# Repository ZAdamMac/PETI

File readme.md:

# PETI Virtual Pet Development Project

## Introduction

PETI is a project to create a bespoke, retro-styled Virtual Pet running on the MSP430FR5994 microcontroller, along with a number of late-project goals to add functionality that is useful for demonstrating the sort of Hardware Hacking concepts useful in (i.e.) DEFCON Badge Challenges.

Full documentation is available as part of the "documentation" directory of this repo. A suite of helper tools is present [here](https://github.com/zadammac/peti-helpers)

This project involves both firmware and hardware development.

## NOTICE: Project on Hiaitus
This project is currently **on hiaitus**. You're stll welcome to submit bug reports (which will be addressed rapidly) or make use of the codebase, but we have a couple of caveats:
- Missing firmware functionality and gameplay features are not currently scheduled to be released. There's some frozen work on the `v/0.6.0` branch and f/ branches originating from it, which starts implementing the next gameplay release.
- It is not currently advisable to mill the development kit boards provided under `hardware`. When the project comes off hiaitus there's going to be a major hardware redesign released, which will be simpler and more elegant.

Currently, we think the project is likely to come off hiaitus sometime around the start of 2027.

## NOTICE: Github End of Life
The version of the project hosted on github is no longer being actively maintained and has been scheduled for truncation (removal of branches and notices apart from this readme file). The authoritative main repository of this project is [Arcana Labs' Forgejo](https://forgejo.arcanalabs.ca/zadammac/peti). Please redirect your upstream branch definitions to that repository. In the days to come, the remaining files from this repository will be removed and purged from the commit history on Github. This has been done because of GitHub's decision to allow for - and encourage - the training of proprietary large language model code generation systems on codebases where the licensing implicitly (or often explicitly) does not permit such conversion.

## Requirements
This project has a number of requirements that need to be satisfied to build the project successfully:
  - It is advised that the developer install TI's Code Composer Studio and its included compiler, or otherwise source cl430 and the rest.
  - The developer will also need to meet the requirements laid out in `hardware_design/readme.md`, and;
  - The developer will need to provide both the standard MSP430 incudes directory and the "driverlib" from MSP430, both available under license from TI.

Specific cloning/installation instructions are included under `documentation/env_setup.md`
	
## Contribution and Acknowledgement

Building PETI has been and will likely continue to be a time-consuming effort. Even at this early stage, some custom hardware has needed to be developed in order to develop the corresponding firmware.

If you would like to contribute to the development of PETI, feel free to submit a pull request, or perhaps buy me a coffee at [ko-fi.com/arclabs](https://ko-fi.com/arclabs), or consider backing [@ZAdamMac on Github Sponsors](https://github.com/users/ZAdamMac/sponsorship.)

## Make Commands
The current version of the makefile (1.0) accepts the following commands:
- `make` - performs a full rebuild of the entire source tree under `src/` and generates an output binary suitable to run on the MSP430FR5994.
- `make clean` - deletes the `build/` dir. Useful for tidying up pre-commit.
- `make target-check` - Outputs information about the currently-connected MSP430FR5994 and/or PETI Dev Kit. Sanity check to ensure a good connection.
- `make target-flash` - Performs the full rebuild then flashes the output binary to the connected PETI dev kit or other MSP430FR5994 target.
- `make target-debug` - Performs a full rebuild, starts the MSP430FR5994 connected by USB in its debugging mode, then uses msp430-dgb to enter debugging mode.
	
## Current State
Please see https://www.arcanalabs.ca/hardware/PETI.html for the latest news on this project.

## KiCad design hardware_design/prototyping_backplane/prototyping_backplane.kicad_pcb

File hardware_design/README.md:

# Explaining the PETI Hardware
As you'll notice when reviewing the KiCAD project files included here, at present, only the layout for the Buttons Daughterboard is fully documented at this time. That is because designing the PETI device as a standalone, single-board item is a down-the-road project, relying on meeting a few other hardware prototyping goals described in the Projects and Wiki sections of the PETI github repo.

At time of writing, the PETI hardware demonstrator consists of:
- The Texas Insturments MSP-EXP430FR994, which is the hardware demonstrator for the MSP430FR5994 microcontroller as well as offering their EX-FET board as an integrated component for programming.
- A Texas Instruments BOOSTXL-SHARP128, which is TI's hardware demonstrator for the Sharp Memory Display used in the project, and;
- A buttons daughterboard.

These three components are attached to one another in a stack using the headers provided on each component.

Check on the status of the projects board before investing in the Hardware. It is possible we have completed our side-goal of providing QEMU emulation of the device.

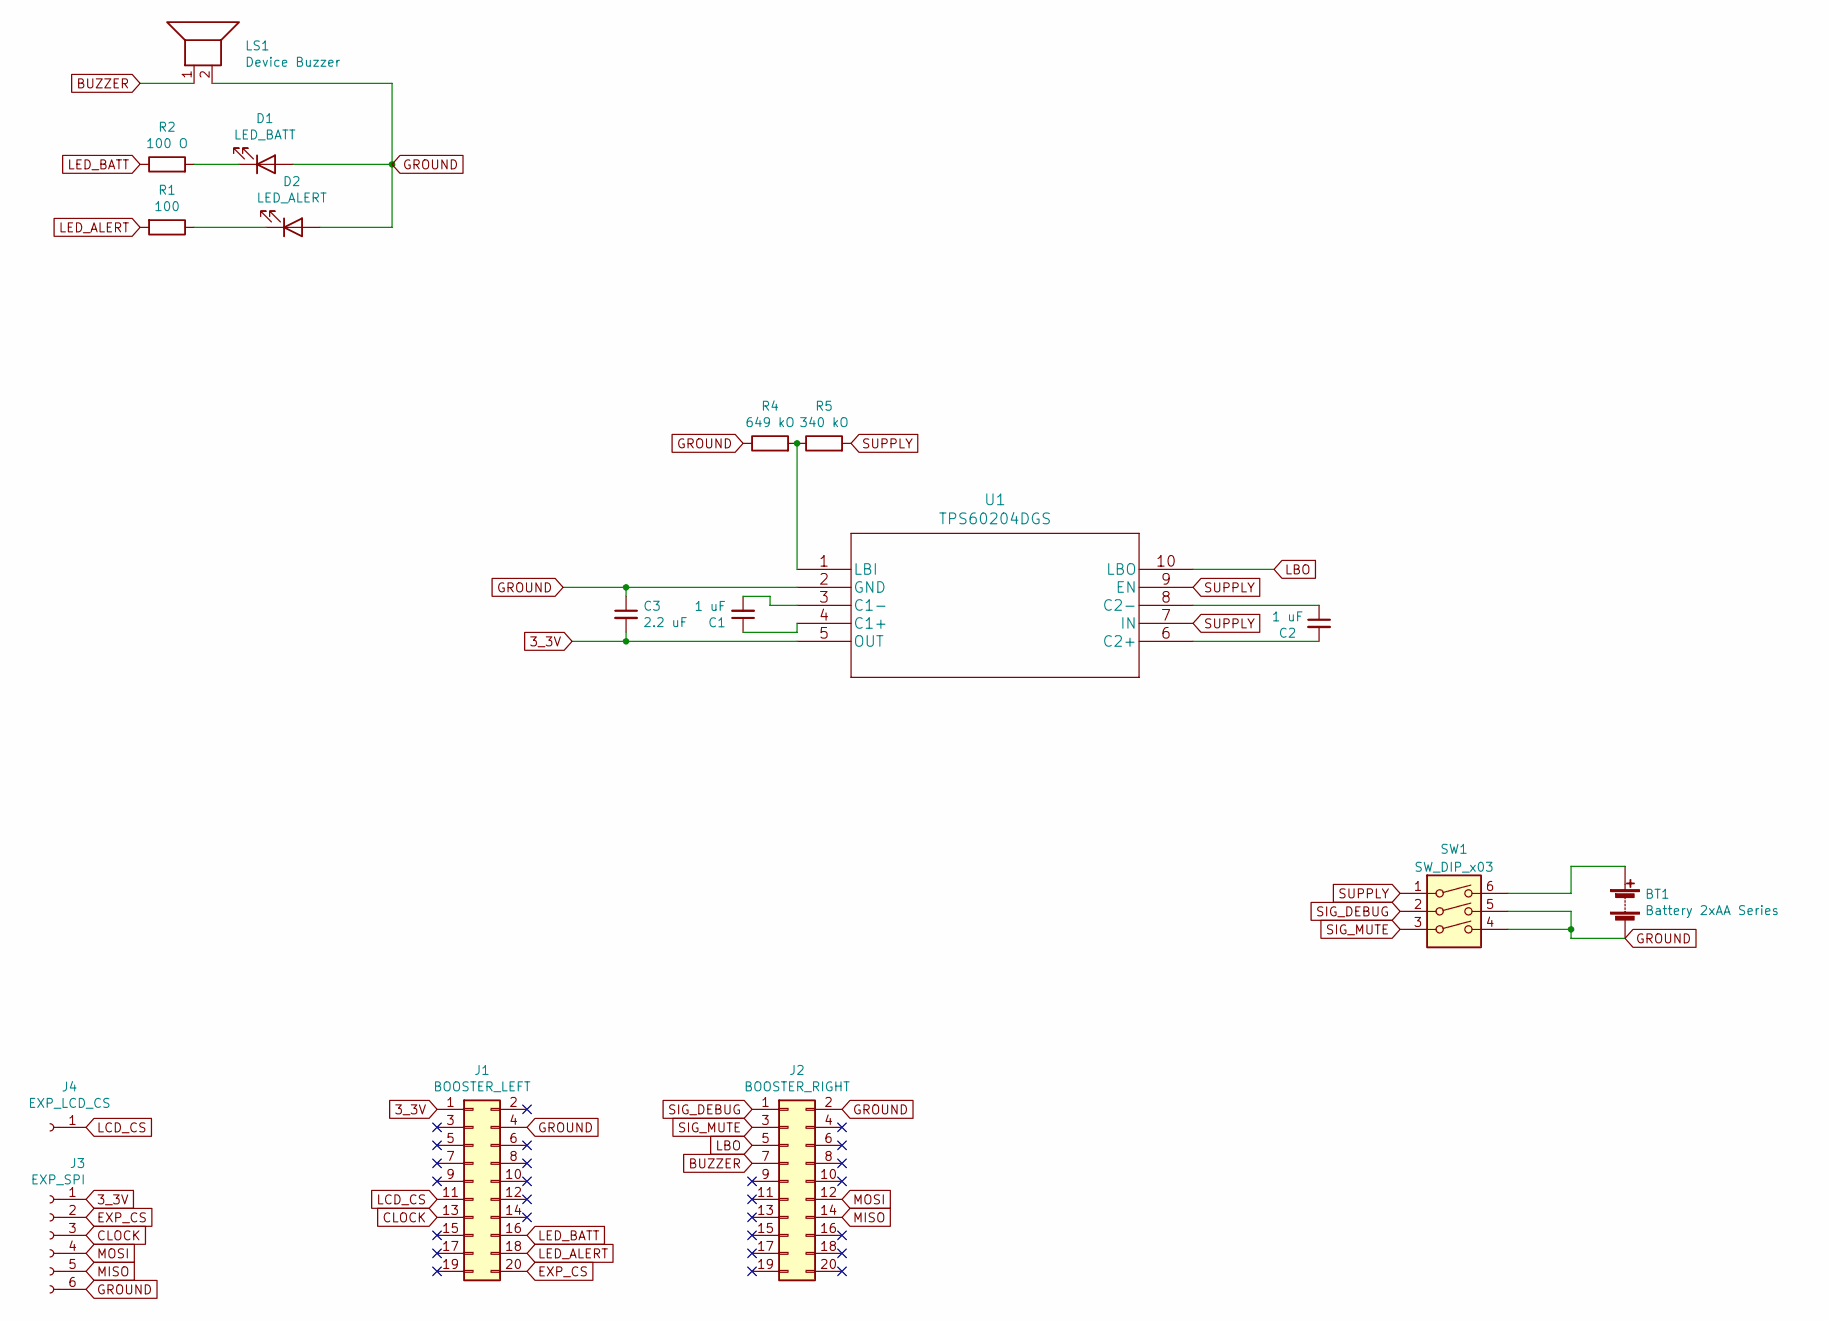
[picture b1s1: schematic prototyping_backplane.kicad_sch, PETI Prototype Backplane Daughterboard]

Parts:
BT1: Battery 2xAA Series; BatteryHolder_Keystone_2462_2xAA
C1, C2: 1 uF; C_Disc_D4.3mm_W1.9mm_P5.00mm
C3: 2.2 uF; C_Disc_D4.3mm_W1.9mm_P5.00mm
D1: LED_BATT; LED_D3.0mm
D2: LED_ALERT; LED_D3.0mm
J1: BOOSTER_LEFT; PinHeader_2x10_P2.00mm_Vertical
J2: BOOSTER_RIGHT; PinHeader_2x10_P2.00mm_Vertical
J3: EXP_SPI; PinHeader_1x06_P2.00mm_Horizontal
J4: EXP_LCD_CS; PinHeader_1x01_P2.54mm_Horizontal
LS1: Device Buzzer; Buzzer_12x9.5RM7.6
R1: 100; R_Axial_DIN0207_L6.3mm_D2.5mm_P7.62mm_Horizontal
R2: 100 O; R_Axial_DIN0207_L6.3mm_D2.5mm_P7.62mm_Horizontal
R4: 649 kO; R_Axial_DIN0207_L6.3mm_D2.5mm_P7.62mm_Horizontal
R5: 340 kO; R_Axial_DIN0207_L6.3mm_D2.5mm_P7.62mm_Horizontal
SW1: SW_DIP_x03; SW_DIP_SPSTx03_Slide_9.78x9.8mm_W7.62mm_P2.54mm
U1: TPS60204DGS; VSSOP-10_3x3mm_P0.5mm

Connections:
3_3V: C3.2, J1.1, J3.1, U1.5 (OUT); also elsewhere on the board
CLOCK: J1.13, J3.3
EXP_CS: J1.20, J3.2
GROUND: BT1.2 (-), C3.1, D1.2 (A), D2.2 (A), J1.4, J2.2, J3.6, LS1.2, R4.1, SW1.4, SW1.5, U1.2 (GND)
LBO: J2.5, U1.10 (LBO); also elsewhere on the board
LCD_CS: J1.11, J4.1
LED_ALERT: J1.18, R1.2
LED_BATT: J1.16, R2.1
MISO: J2.14, J3.5
MOSI: J2.12, J3.4
unnamed: BT1.1 (+), SW1.6
unnamed: D1.1 (K), R2.2
unnamed: D2.1 (K), R1.1
unnamed: C1.1, U1.4 (C1+)
unnamed: C1.2, U1.3 (C1-)
unnamed: C2.2, U1.6 (C2+)
unnamed: C2.1, U1.8 (C2-)
unnamed: R4.2, R5.1, U1.1 (LBI)
SIG_DEBUG: J2.1, SW1.2
SIG_MUTE: J2.3, SW1.3
SUPPLY: R5.2, SW1.1, U1.7 (IN), U1.9 (EN)

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
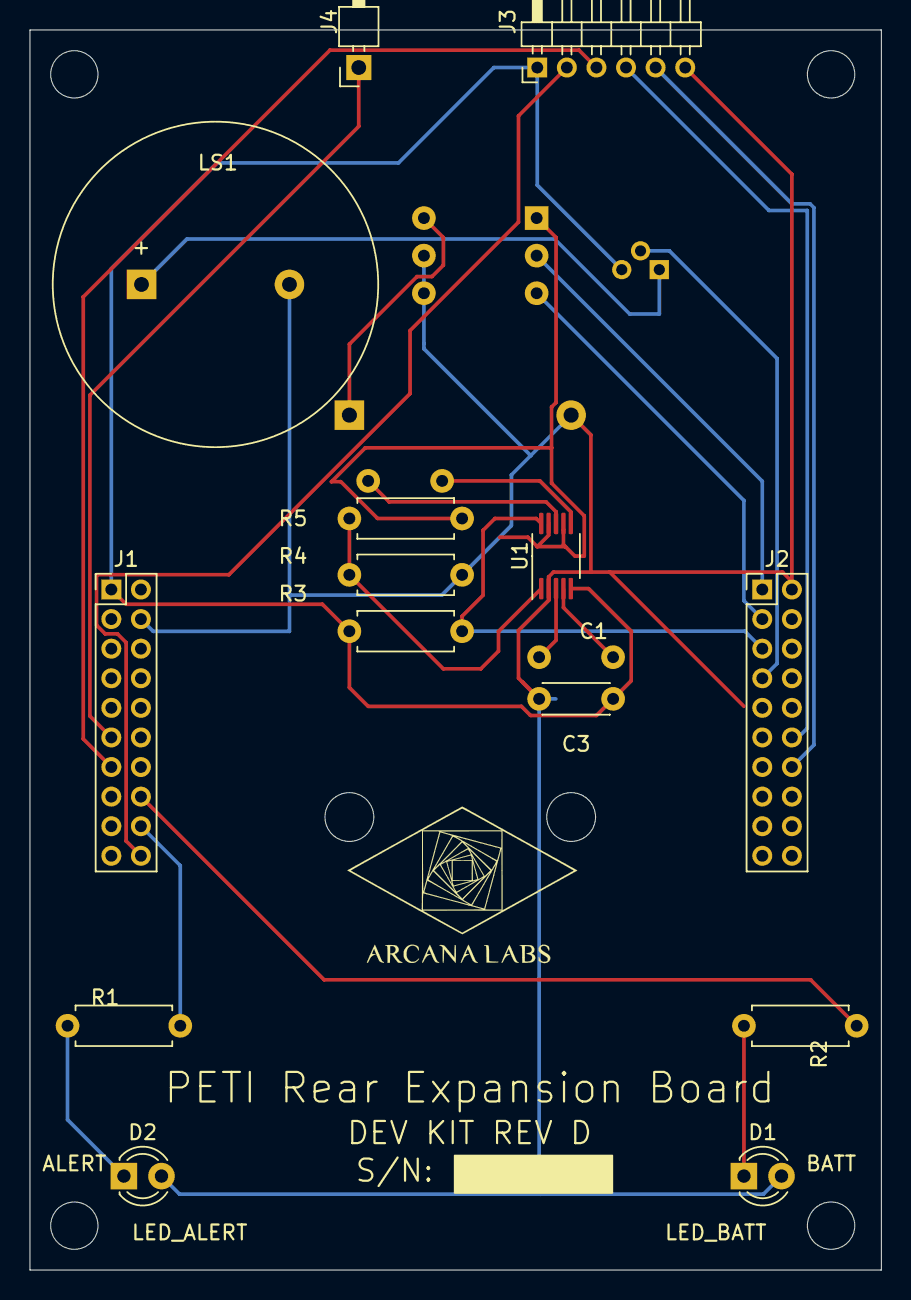
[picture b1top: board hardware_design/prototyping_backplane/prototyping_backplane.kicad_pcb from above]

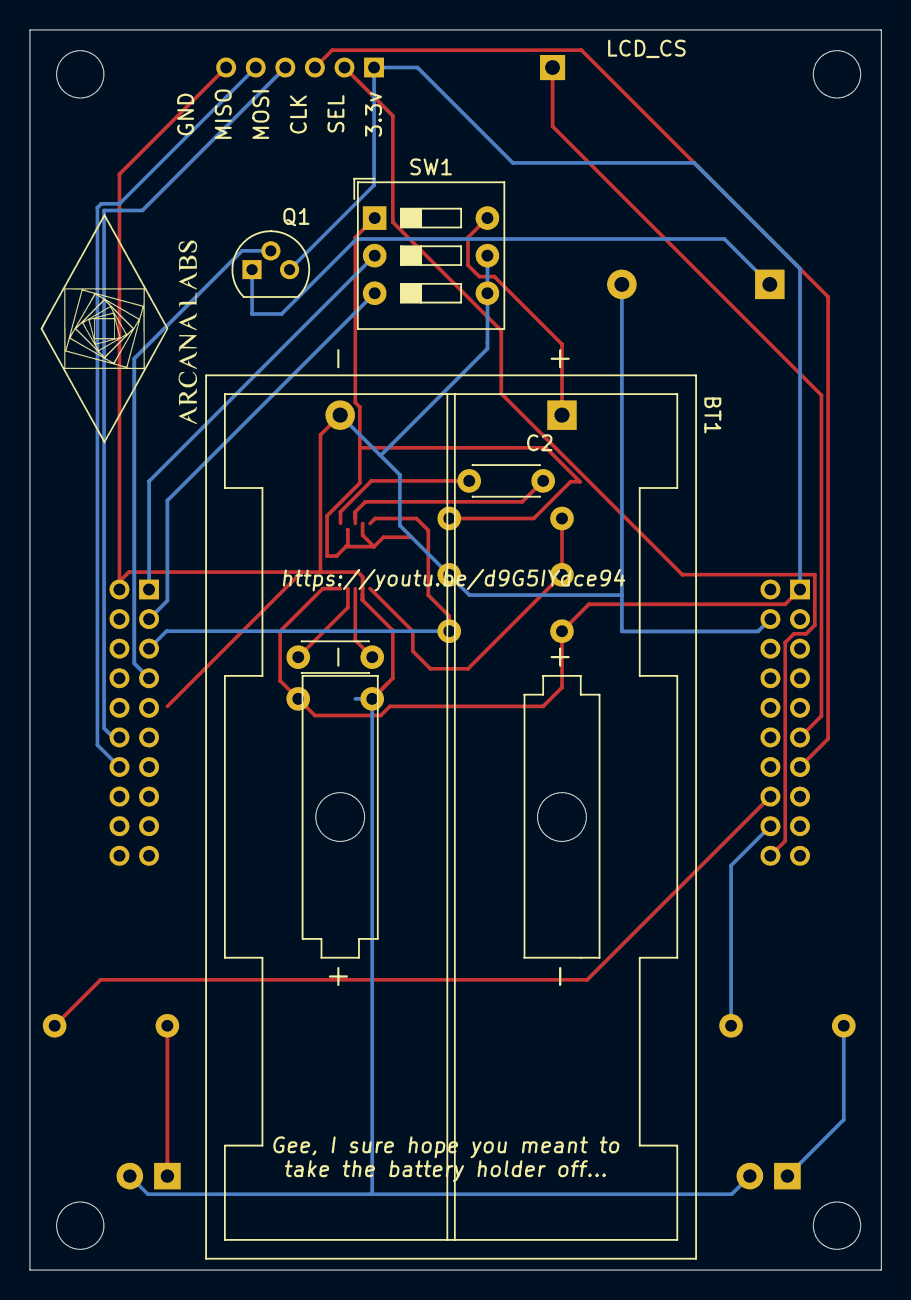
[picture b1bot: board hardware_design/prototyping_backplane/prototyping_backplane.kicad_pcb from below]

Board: 2 copper layers, 57.6 x 83.8 mm, 21 parts (5 on the bottom side), 23 nets.

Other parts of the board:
ALERT: MountingHole_3.2mm_M3
BATT: MountingHole_3.2mm_M3
Q1: 2N2222A; TO-92
R3: 100 kO; R_Axial_DIN0207_L6.3mm_D2.5mm_P7.62mm_Horizontal

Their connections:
3_3V: Q1.3 (C), R3.2; also elsewhere on the board
LBO: R3.1; also elsewhere on the board

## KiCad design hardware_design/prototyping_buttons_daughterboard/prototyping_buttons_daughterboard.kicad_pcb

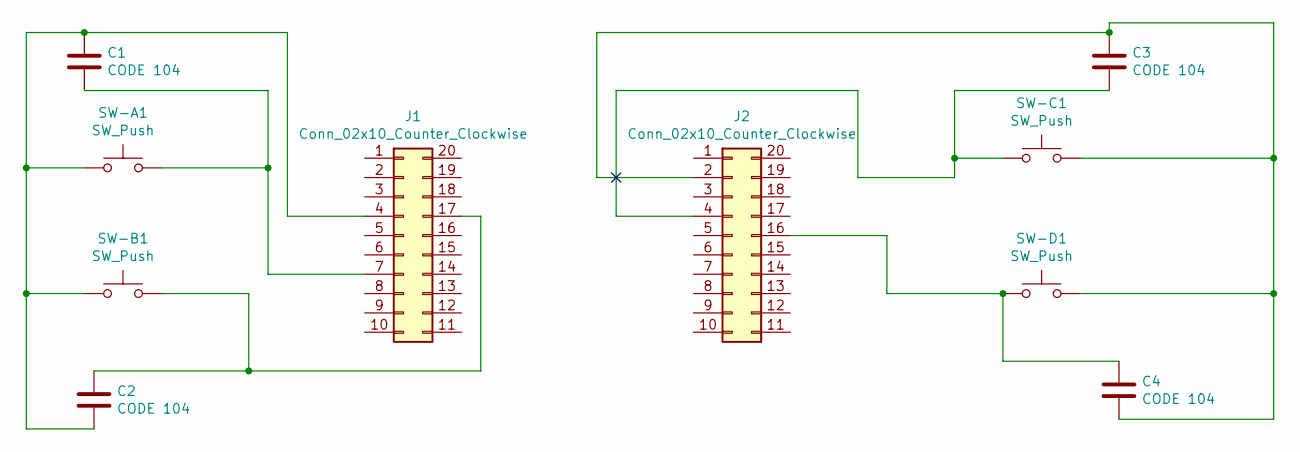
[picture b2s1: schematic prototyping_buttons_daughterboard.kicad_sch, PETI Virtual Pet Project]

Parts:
C1, C2, C3, C4: CODE 104; C_Disc_D3.0mm_W2.0mm_P2.50mm
J1, J2: Conn_02x10_Counter_Clockwise; PinSocket_2x10_P2.54mm_Vertical
SW-A1: SW_Push; SW_PUSH_6mm
SW-B1: SW_Push; SW_PUSH_6mm
SW-C1: SW_Push; SW_PUSH_6mm
SW-D1: SW_Push; SW_PUSH_6mm

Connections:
unnamed: C2.1, J1.17, SW-B1.2
unnamed: C3.1, C4.2, J2.2, SW-C1.2, SW-D1.2
unnamed: C3.2, J2.4, SW-C1.1
unnamed: C4.1, J2.16, SW-D1.1
unnamed: C1.1, C2.2, J1.4, SW-A1.1, SW-B1.1
unnamed: C1.2, J1.7, SW-A1.2

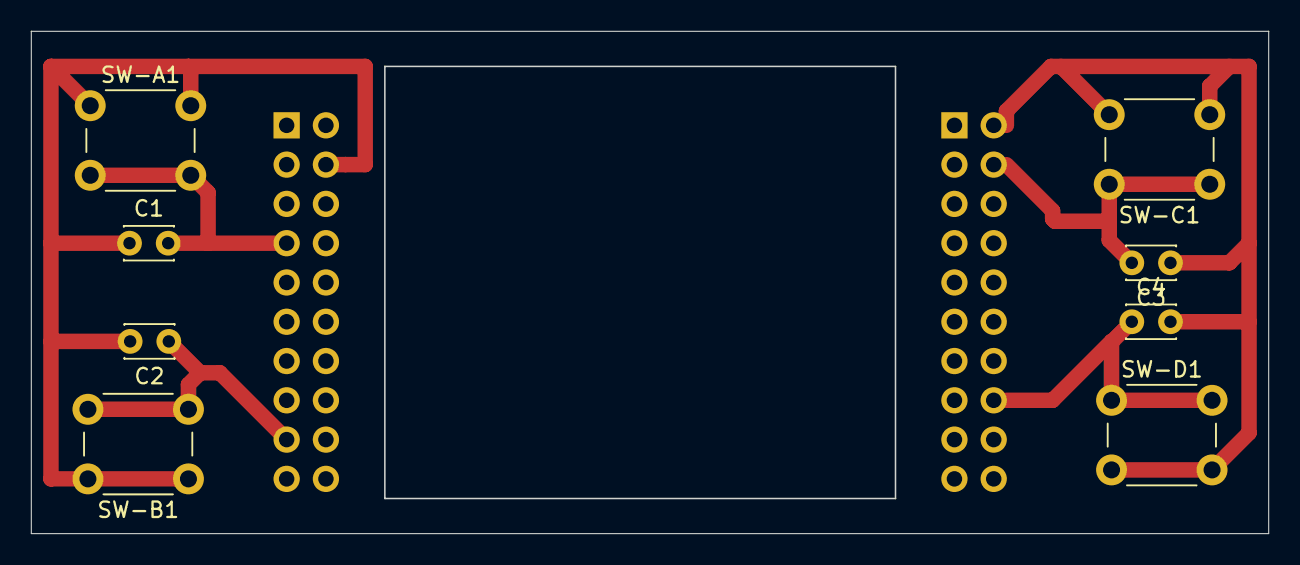
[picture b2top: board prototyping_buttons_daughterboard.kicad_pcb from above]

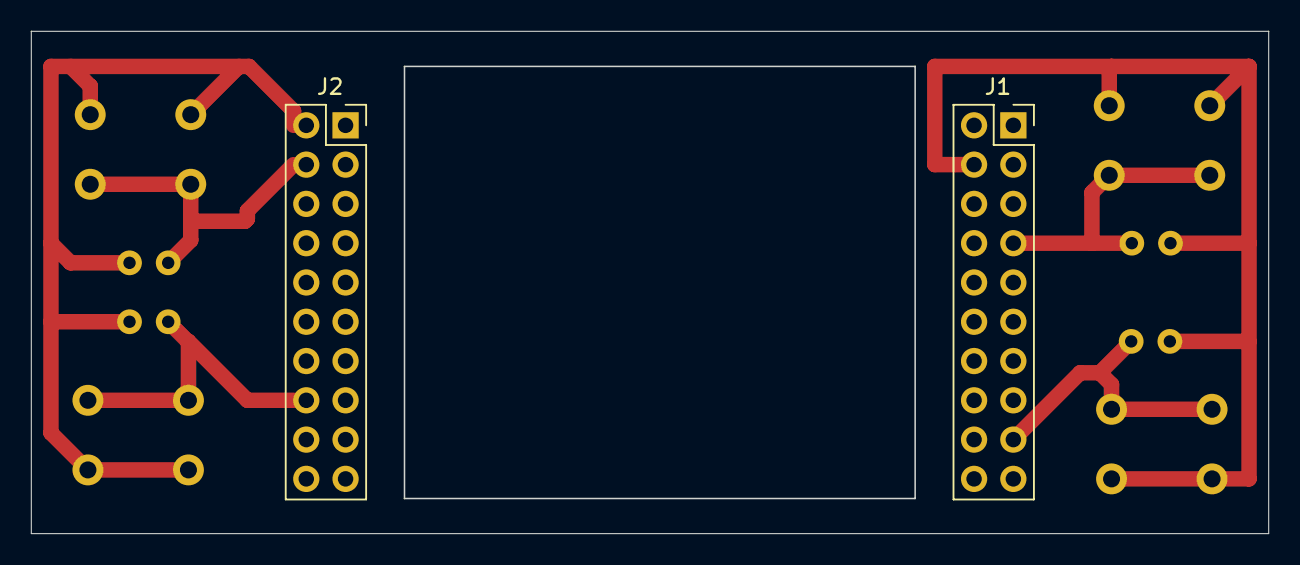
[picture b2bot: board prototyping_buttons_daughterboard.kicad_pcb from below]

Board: 2 copper layers, 80.0 x 32.5 mm, 10 parts (2 on the bottom side), 6 nets.

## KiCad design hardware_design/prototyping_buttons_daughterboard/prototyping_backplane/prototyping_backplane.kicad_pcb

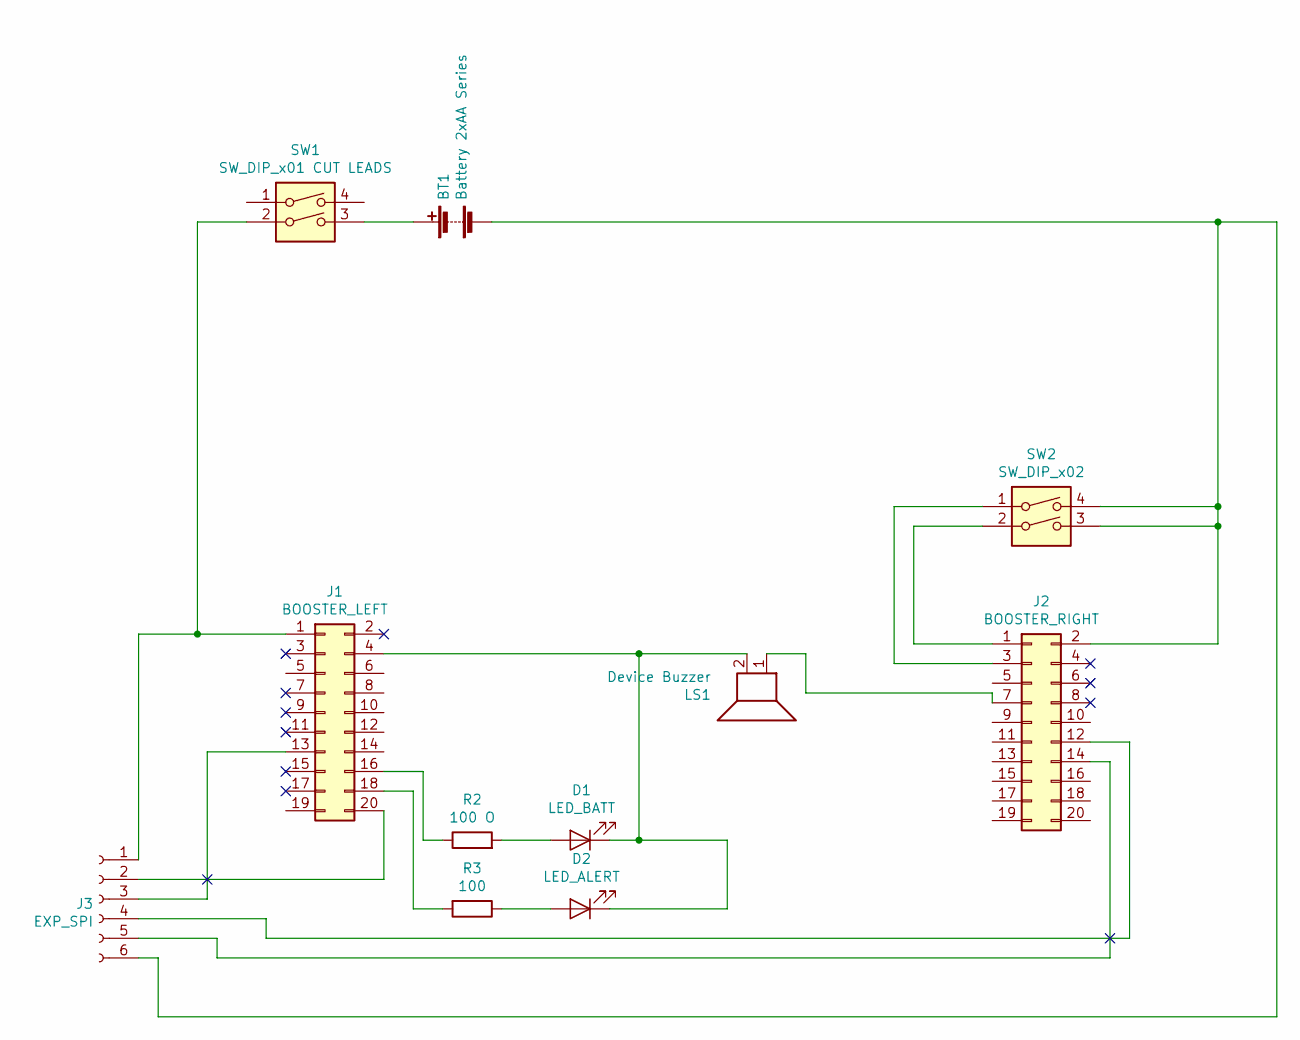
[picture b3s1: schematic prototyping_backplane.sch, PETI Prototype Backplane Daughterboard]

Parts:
BT1: Battery 2xAA Series; BatteryHolder_Keystone_2462_2xAA
D1: LED_BATT; LED_D3.0mm
D2: LED_ALERT; LED_D3.0mm
J1: BOOSTER_LEFT; PinHeader_2x10_P2.00mm_Vertical
J2: BOOSTER_RIGHT; PinHeader_2x10_P2.00mm_Vertical
J3: EXP_SPI; PinHeader_1x06_P2.00mm_Horizontal
LS1: Device Buzzer; Buzzer_12x9.5RM7.6
R2: 100 O; R_Axial_DIN0204_L3.6mm_D1.6mm_P5.08mm_Horizontal
R3: 100; R_Axial_DIN0204_L3.6mm_D1.6mm_P5.08mm_Horizontal
SW1: SW_DIP_x01 CUT LEADS; SW_DIP_SPSTx02_Slide_6.7x6.64mm_W7.62mm_P2.54mm_LowProfile
SW2: SW_DIP_x02; SW_DIP_SPSTx02_Slide_6.7x6.64mm_W7.62mm_P2.54mm_LowProfile

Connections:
unnamed: BT1.1 (+), SW1.3
unnamed: BT1.2 (-), J2.2, J3.6, SW2.3, SW2.4
unnamed: D1.1 (K), D2.1 (K), J1.4, LS1.2
unnamed: D1.2 (A), R2.2
unnamed: D2.2 (A), R3.1
unnamed: J1.1, J3.1, SW1.2
unnamed: J1.13, J3.3
unnamed: J1.16, R2.1
unnamed: J1.18, R3.2
unnamed: J1.20, J3.2
unnamed: J2.1, SW2.2
unnamed: J2.3, SW2.1
unnamed: J2.7, LS1.1
unnamed: J2.12, J3.4
unnamed: J2.14, J3.5

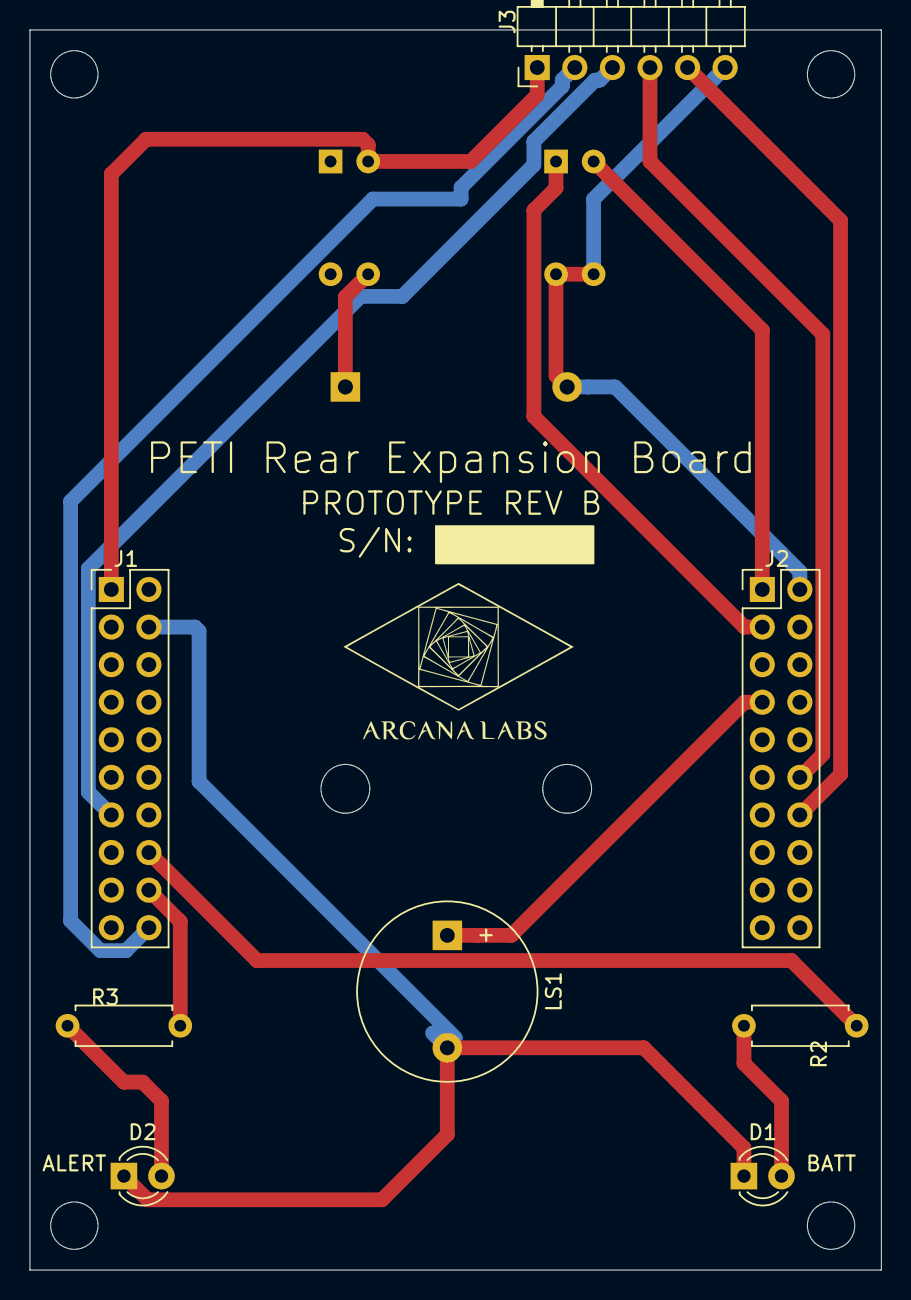
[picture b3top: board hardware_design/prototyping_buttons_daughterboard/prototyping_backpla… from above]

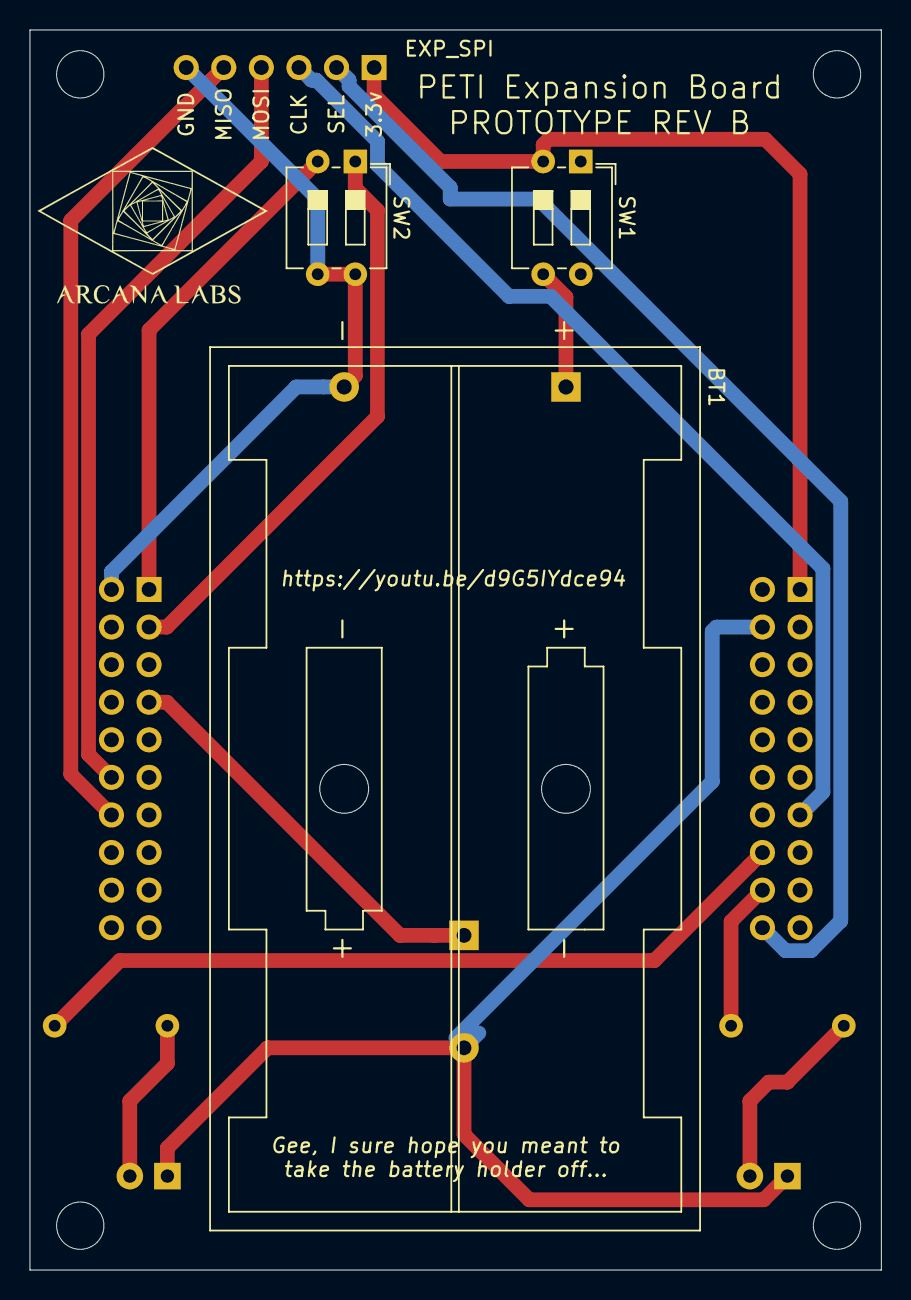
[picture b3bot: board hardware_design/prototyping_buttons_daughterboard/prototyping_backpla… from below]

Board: 2 copper layers, 57.6 x 83.8 mm, 13 parts (3 on the bottom side), 15 nets.

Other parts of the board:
ALERT: MountingHole_3.2mm_M3
BATT: MountingHole_3.2mm_M3

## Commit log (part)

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2020-10-11 Initial commit Changes to be committed: new file: lib/display/display.c new file: lib/display/display.h new file: lib/display/font.h new file: lib/display/splash.h new file: main.c
    Working version of displaySplash() with working uptime POC.
2020-11-27 On branch master Your branch is up to date with 'origin/master'. Changes to be committed: modified: lib/display/display.c modified: lib/display/font.h new file: lib/display/fontedit source files/font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
    -Adds source files for the stored fonts for use with FontEdit.
    -Alters Print_Text() to use the new format for font8x8
    -Updates font8x8; however this is not usefully changed, and a future update will be needed.
2020-11-27 Changes to be committed: modified: lib/display/display.c - Main SPIWrite does not reverse and negate/complement bytes any more. - PrintText has been altered to use the logic of the new font format. -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
2020-11-28 Changes to be committed: modified: lib/display/display.c - refactored PrintText to PrintTextSmall for clarity - added/tested PrintTextMedium - added/tested PrintTextLarge modified: lib/display/displa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
2020-12-04 Changes to be committed: modified: lib/display/display.c - deprecated the "padded" clauses in all three print functions. modified: main.c - added the necessary frameworks for the input/output proof o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
2020-12-13 Changes to be committed: new file: CODE_OF_CONDUCT.md new file: CONTRIBUTING.md new file: LICENSE new file: readme.md
2020-12-18 Changes to be committed: new file: hardware_design/prototyping_buttons_daughterboard/fp-info-cache new file: hardware_design/prototyping_buttons_daughterboard/gerber/prototyping_buttons_daughterboard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
2020-12-24 Changes to be committed: new file: documentation/display.md new file: documentation/fonts.md new file: documentation/main.md modified: readme.md
2020-12-24 Changes to be committed: new file: hardware_design/README.md new file: hardware_design/prototyping_buttons_daughterboard.zip modified: hardware_design/prototyping_buttons_daughterboard/fp-info-cache 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
2020-12-28 Adjusted indentation in main()
2020-12-28 Turned commented section into ifdef section
2020-12-28 Made uptime its own function
2020-12-28 Broke init into two more functions
2020-12-28 minor ISR cleanup
2020-12-28 Moved line comments above in main
2020-12-28 Removed commented out code
2021-05-08 Syncing to remote, step 1
2021-05-08 sync part 2
2021-05-08 modified: lib/display/splash.h fixed line weights on the image itself
2021-05-08 modified: main.c - changed the timerA0 interrupt to trigger once per second (improves graphical performance)
2021-05-09 main.c: - added RTC initialization to a default time - removed the basic uptime tracking based on incrementing arbitrary pointers - changed uptime display on the demo screen to use the time stored in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
2021-05-09 main.c - Fixes a modular math bug based on the "BCD" calendar data format.
2021-05-10 Changes to be committed: modified: lib/display/display.h modified: lib/display/splash.h - defs now sit correctly inside the block new file: lib/hwinit/hwinit.c new file: lib/hwinit/hwinit.h - moves t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
2021-05-10 Changes to be committed: modified: lib/display/display.c modified: lib/display/display.h - adds the functionality to display different screen types based on a universal struct modified: lib/hwinit/hw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
2021-05-11 Changes to be committed: modified: lib/display/display.c modified: lib/display/display.h - adds a handler for MODE_MENU, a display type consisting of up to 10 rows of 8x12 text. modified: lib/display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
2021-05-13 Adds the main_game scene and games_manager, including updates to leverage this functionality. Sets version to 0.0.1, but release is not ready until this branch is merged. This update implements the m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
2021-05-15 Linting and minor tweaks, validated on hardware.
2021-05-24 Update readme.md
    Update branding.
2021-05-26 modified: lib/hwinit/hwinit.c -increase SMCLK to 8Mhz and change the dividers to change the timer interrupt frequency to 2/second -closes an issue where the screen refresh is very very slow. modified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
2021-05-26 add printTextLarge_enhanced, and support for it, so that character mirroring and character inversion can be used for screen drawing.
2021-07-28 Changes to be committed: modified: lib/display/font.h modified: lib/display/fontedit source files/front16x16.fnt - adds the full character set to the 16x16 display font. new file: lib/game/evo_data.c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
2021-10-29 See changelog - v 0.0.4
2021-11-02 Completed work for statusmenu.
2021-11-02 fix missed revert to default for discipline level
2021-11-10 Update to version 0.0.5. Last update before refactor. See changelog.
2021-11-10 fixed the missing menu generator
2021-11-13 0.0.5r2 revisions. See changelog.
2021-11-13 missed changelog entry
2021-11-14 add new display logic/cut menu_generator over to new method
2021-11-21 Overhaul of the display driver system. All scenes that relied on Display_Frame have been rewritten to use the new struct, with the exception of Demo Mode. See Changelog.
2021-11-21 Update version number
2021-11-30 Publish Backboard in Rev B close issue 17
2021-12-17 add the eating and feeding subsystem; see changelog
2021-12-17 Yeah, that changelog
2022-01-18 enable GPIO for buzzer and LEDS
2022-01-18 Add the audio alert primitive for pulses of various lengths
2022-01-18 Add the Timer B ISR
2022-02-01 Increment to dev version, add basic hardware functionality for audio, add simple sound test
2022-02-01 Blinkenlights primitives and alert API
2022-02-01 add mute hardware mute on SW2.1
2022-02-16 enable debug menu
2022-02-16 gate enablement of debug mode between SW 2.2 being closed
2022-02-16 egg mode bypass is automatic when sw 2.2 is closed. egg is again the default stage.
2022-03-03 refactor extant scenes to add the font selection logic.
2022-03-03 closes issue 19
2022-03-03 final pre-hw-commit 0.1.0
2022-09-23 Commit in the RNG primitives; update changelog; freeze driverlib.
2022-10-11 Move source files to dedicated directory
2022-10-11 add boilerplate makefiles
2022-10-12 Removing spaces from paths for make compatibility
2022-10-12 Yeeting Make
2022-10-12 Update CONTRIBUTING.md with new branching guidance
2022-11-11 assorted tidying; replace vetted makefile.
2022-11-11 Add flash functionality back into makefile
2022-11-11 Add documentation for new make tiers.
2022-11-11 H/jailbreak ccs (#23)
    * Move source files to dedicated directory
    * add boilerplate makefiles
    * Removing spaces from paths for make compatibility
    * Yeeting Make
    * Update CONTRIBUTING.md with new branching guidance
    * assorted tidying; replace vetted makefile.
2022-12-09 #24: Increase periodicity of the RNG
2023-05-09 Working updates through end of may
2023-05-24 F/version0 1 1 (#27)
    * Move source files to dedicated directory
    * add boilerplate makefiles
    * Removing spaces from paths for make compatibility
    * Yeeting Make
    * Update CONTRIBUTING.md with new branching guidance
    * assorted tidying; replace vetted makefile.
2023-05-24 the binary object should never have been commited in the first place
2023-05-24 correct merge conflicts;correct bug #28
2023-06-15 RPS core logic; generalize function for modding HUNGER_FUN
2023-06-19 add size symbols to evodata.h
2023-06-20 Add the attractive animations and sound to the RPS minigame and elements to support that
2023-06-20 Correct hardlock introduced by moving input handling by putting it back
2023-07-07 Consolidate files to the last benchmarks for the 0.2.0 release.
2023-07-07 increment version string
2023-07-07 Update default date for release prep.
2023-07-07 Update contributing to supprt v/ branches and comment conventions
2023-07-07 Update Changelog
2023-07-23 catchup of documentation-related work
2023-07-23 forgot to export the pdf
2023-09-07 preventative fix for poss. log. bug in display frame compute
2023-09-11 Changes to implement game state saving. Users with exiting save data since last flash now prompted to restore or delete
2023-09-14 changes to get blinkenlights to actually blink.
2023-09-19 Add preprocessor directive to facilitate debugging compliation errors.
2023-09-19 Add LCD sleep functionality and related improvements.
2023-09-20 Support for low battery Indication.
2023-09-24 Fixes Issue 34
2023-09-24 Commit in corrected TODO/FUTURE tags.
2023-09-24 final firmware for 0.3.0. Personally tested on hardware
2023-09-24 Update schematics for revision D to close issue 35. PCB not complete, see release notes.
2023-09-27 Updates to support the pet sleeping: - Pet no longer evaluates for alerts or status degredation while asleep - Pet enters and exits sleep based on cerfews set in game_manager.h - started refactoring 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
2023-10-04 necessary changes to add sleeping animations to main_game.c
2023-10-05 pet now cannot play games while sleepwalking.
2023-10-06 Lightbulb mode.
2023-10-06 Fix menu bug.
2023-10-06 Add wakeup alert; fix sleepy screen bug from previous commit.
2023-10-17 Correct sleeping animations.
2023-10-17 Resolve outstanding branch todos
2023-10-17 update branch version string
2023-10-17 update version to branch name
2023-10-26 metanimations updates
2023-11-22 Refactor Stage struct to allow metanimation and font addressing.
2024-02-06 Fixes issue 40
2024-02-06 adds support for distributed fonts
2024-02-06 Add font uniselector
2024-02-06 Bake in the 4 exiting fonts in the new format.
2024-02-06 Final cleanup of font-related data
2024-02-06 update make details for font headerfile automation
2024-02-06 clean up unofficial tool files
2024-02-22 add evolution's most basic form
2024-02-24 Fix bug that was causing issues with sleep bounding
2024-02-24 comment in previous changes; add fix for out of bounds evolution times
2024-02-25 add age and evolution options to the debug menu
2024-02-25 forgot to update changelog for previous commits
2024-03-03 Retrofit eating scenes to include font addressing
2024-03-12 Repair font16x16_1; correct evo data, game manager. Start work on RPS bug
2024-05-17 correct issue #38
2024-06-02 Add the working evolution scene
2024-06-02 Fix verdef
2024-06-02 Address TODOs targeted for this release.
2024-06-02 update service manual
2024-06-02 fix release version
2024-11-21 Fix issue 45
2024-11-21 fix version string
2024-12-04 Resolve issue 38; replace bad code in MG-RPC with strcpy
2025-01-16 Update version string and default date for release
2025-01-23 update/finalize revD backplanes
2025-01-30 Change AUDIO_pulse to use PWM on B0 with A2 now handling length
2025-02-12 PWM Documentation
2025-02-20 add GAME_NEEDS_evaluatePooped and associated definitions
2025-03-01 add poop primitives; needs tuning; breaks main game display logic
2025-03-01 this is the real poop logic
2025-03-06 amend font16x16_1 to include poop and bathing icons
2025-03-06 Amend poop draw function to use global icons and pretty-print; elim magic numbers.
2025-03-06 Start an icon defintion header for future magic number removals
2025-03-10 TODO Elimination
2025-03-10 Add washlet option to MG menu; fix exposed bug in MG_computeBottomDirective
2025-03-11 Add bathing capability
2025-03-11 correct missing refstrings
2025-03-11 enable output from RNG to EXP_SPI
2025-03-11 Tuned the probabilities
2025-03-17 Replace MG_placeStatusIcons; add MG_directStatusIcons; add status icons to icons.h
2025-03-17 Rework MG_updatePlayfieldSleeping to use the new statusIcons
2025-03-18 replaces older logic for drawing status icons with positional logic
2025-03-18 changelog.md
2025-03-18 add sleep edge-detection and matching alert
2025-03-18 add timeout delay to menu_generator; set to 15 frames//roughly 15 seconds.
2025-03-18 bake in doc updates
2025-03-18 final housekeeping
2025-04-23 set dev VERSION
2025-05-13 corrects for the menu bug
2025-05-13 Complete upgrades to Evo Data Definitions
2025-05-13 erases unnecessary todo
